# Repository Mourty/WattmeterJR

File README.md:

# WattmeterJR

This is a smaller cheaper version of the wattmeter described here https://github.com/Mourty/Wattmeter-Project

This version of the measurment board is greatly different than the original and required seperate firmware, but can interface with the service from the original just fine. This version doesn't have the super capacitor and boost converter. It also forgoes the voltage transformer in favor of a voltage divider. All parts that can be surface mount are. This is to save space and cost. The ESP32 used here also isn't a dev module and doesn't have the normal USB interface and requires a seperate UART programming device.

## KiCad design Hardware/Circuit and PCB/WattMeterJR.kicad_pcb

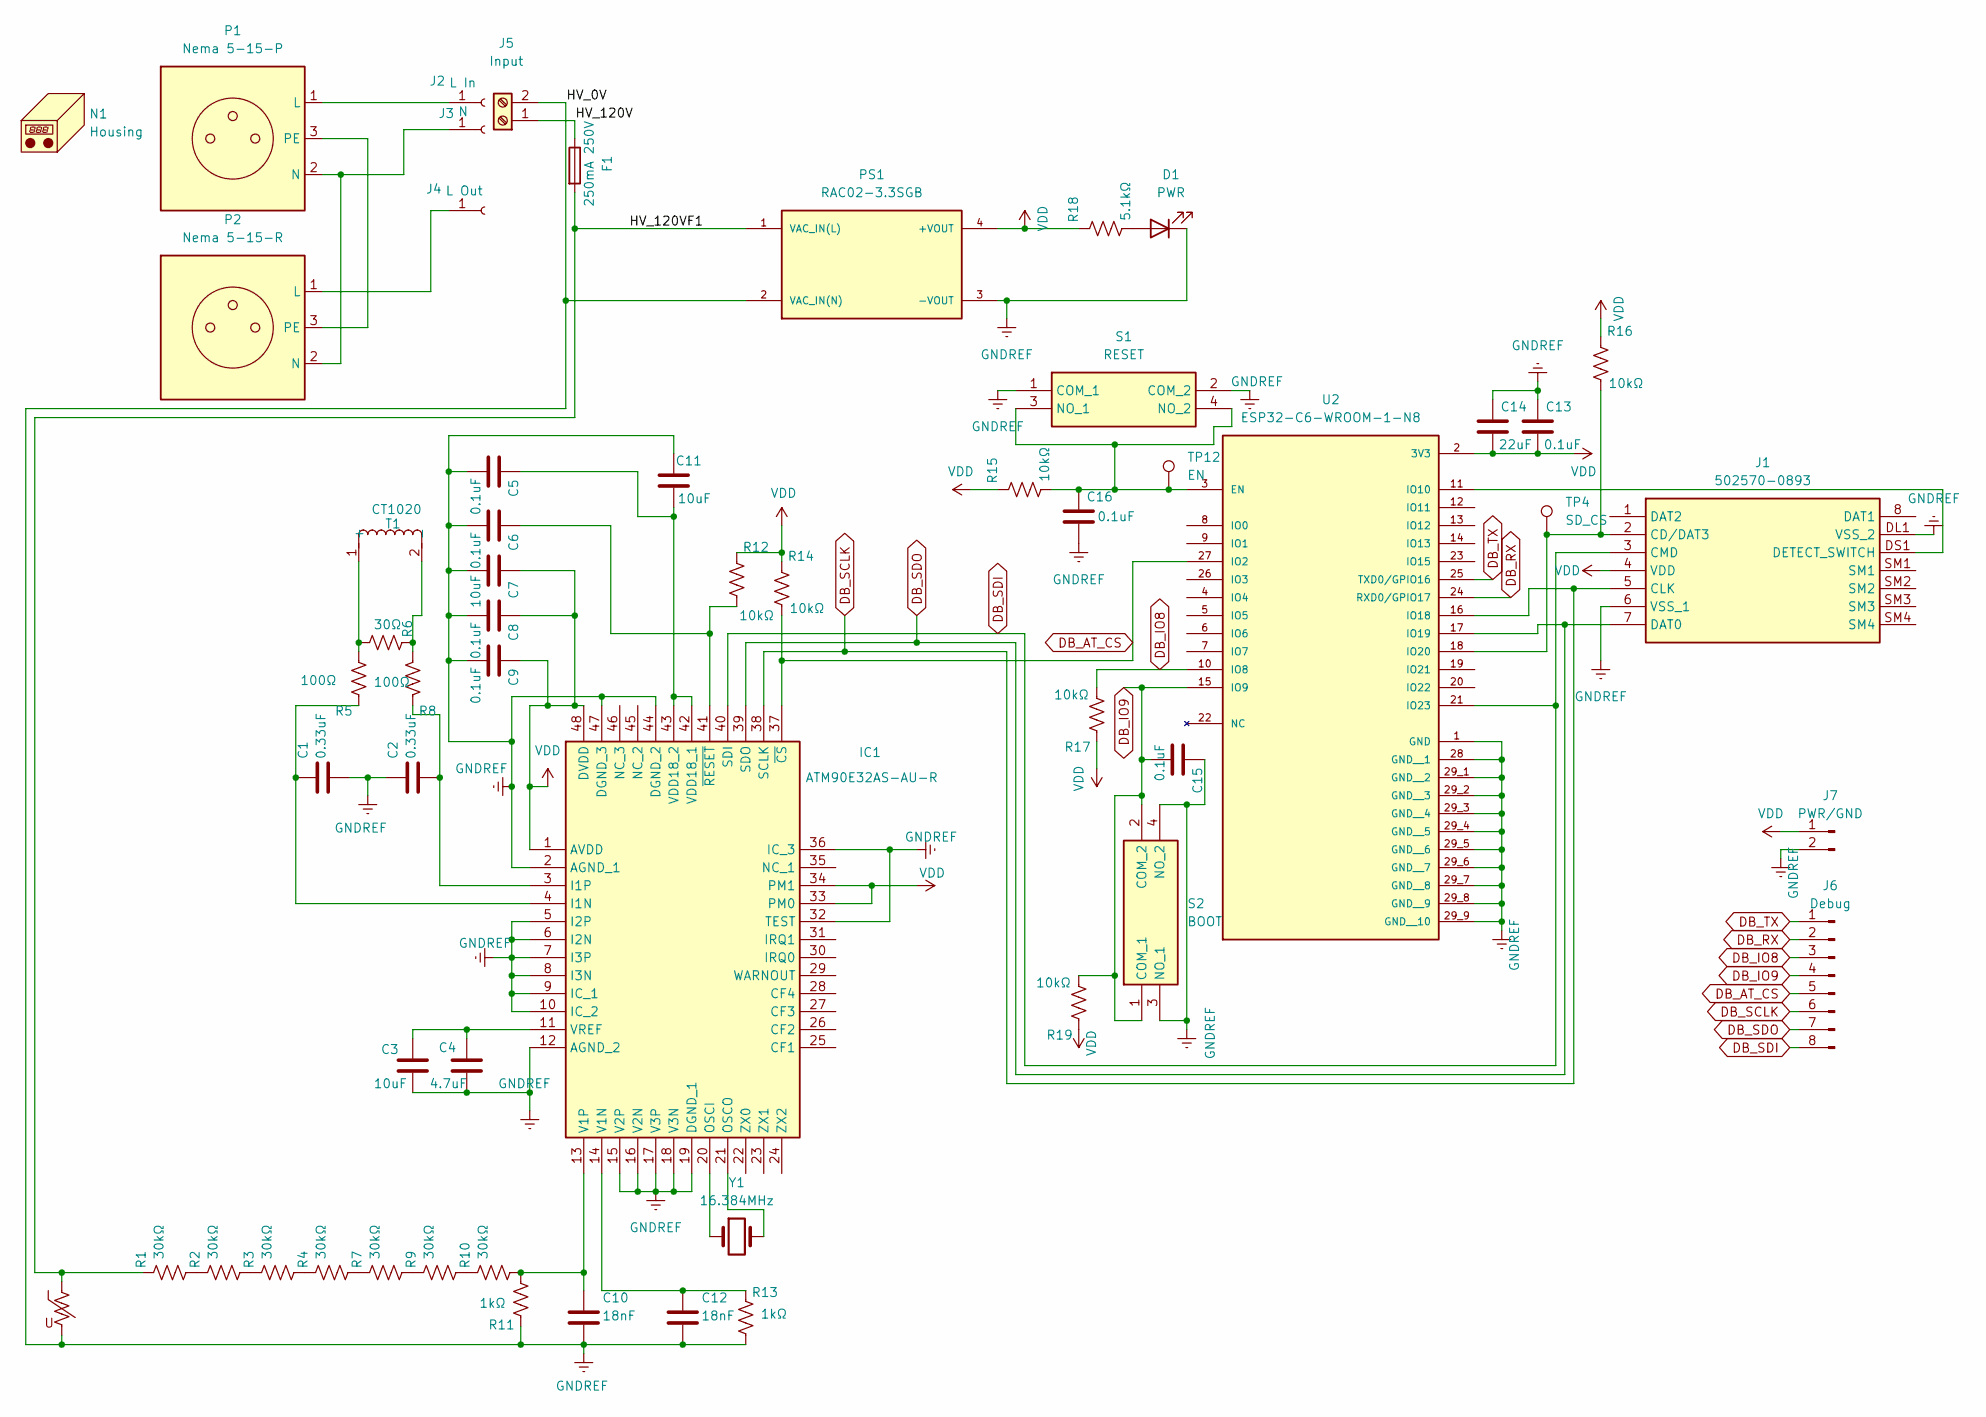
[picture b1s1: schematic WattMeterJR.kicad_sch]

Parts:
C1, C2: 0.33uF; C_0805_2012Metric_Pad1.18x1.45mm_HandSolder; Mouser# 810-FG18X7R1H334KRT6
C3, C7, C11: 10uF; C_0805_2012Metric_Pad1.18x1.45mm_HandSolder; Mouser# 810-FG18X5R1E106MR00
C4: 4.7uF; C_0805_2012Metric_Pad1.18x1.45mm_HandSolder; Mouser# 810-FG28X5R1E475KRT6
C5, C6, C8, C9, C13, C15, C16: 0.1uF; C_0805_2012Metric_Pad1.18x1.45mm_HandSolder; Mouser# 594-K104K15X7RF5WH5
C10, C12: 18nF; C_0805_2012Metric_Pad1.18x1.45mm_HandSolder; Mouser# 594-K183K10X7RF53H5
C14: 22uF; C_0805_2012Metric_Pad1.18x1.45mm_HandSolder; Mouser# 594-K104K15X7RF5WH5
D1: PWR; LED_0805_2012Metric_Pad1.15x1.40mm_HandSolder
F1: 250mA 250V; 00318231; Mouser# 576-0313.250HXP
IC1: ATM90E32AS-AU-R; QFP50P900X900X120-48N; Mouser# 556-ATM90E32AS-AU-R
J1: 502570-0893; 5025700893; Mouser Part Number 538-502570-0893
J2: L In
J3: N
J4: L Out
J5: Input; CUI_TB005-762-02BE; Mouser# 490-TB005-762-02BE
J6: Debug; PinHeader_1x08_P2.54mm_Vertical
J7: PWR/GND; PinHeader_1x02_P2.54mm_Vertical
N1: Housing; 1591XXSBK
P1: Nema 5-15-P
P2: Nema 5-15-R
PS1: RAC02-3.3SGB; CONV_RAC02-3.3SGB; PARTREV 1
R1, R2, R3, R4, R7, R9, R10: 30kΩ; R_0805_2012Metric_Pad1.20x1.40mm_HandSolder
R5, R8: 100Ω; R_0805_2012Metric_Pad1.20x1.40mm_HandSolder
R6: 30Ω; R_0805_2012Metric_Pad1.20x1.40mm_HandSolder
R11, R13: 1kΩ; R_0805_2012Metric_Pad1.20x1.40mm_HandSolder
R12, R14, R15, R16, R17, R19: 10kΩ; R_0805_2012Metric_Pad1.20x1.40mm_HandSolder
R18: 5.1kΩ; R_0805_2012Metric_Pad1.20x1.40mm_HandSolder
RV1: 130VAC; C_Disc_D8.0mm_W5.0mm_P5.00mm; Mouser# 576-V07E130P
S1: RESET; PTS526SK15SMTR2LFS; Mouser Part Number 611-PTS526SK15SMR2L
S2: BOOT; PTS526SK15SMTR2LFS; Mouser Part Number 611-PTS526SK15SMR2L
T1: CT1020; Manufacturer_Part_Number CS1100L; Digikey# 419-CT1020-ND
TP4: SD_CS; PinHeader_1x01_P2.54mm_Vertical
TP12: EN; PinHeader_1x01_P2.54mm_Vertical
U2: ESP32-C6-WROOM-1-N8; XCVR_ESP32-C6-WROOM-1-N8; PARTREV 1.0
Y1: 16.384MHz; Crystal_HC49-U_Vertical; Mouser# 815-ABL-16.384-B2

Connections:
/HV_120V: F1.1, J5.1
/HV_120VF1: F1.2, PS1.1 (VAC_IN(L)), R1.2, RV1.1
DB_AT_CS: IC1.37 (~CS), J6.5, R14.1, U2.27 (IO2)
DB_IO8: J6.3, R17.1, U2.10 (IO8)
DB_IO9: C15.2, J6.4, R19.1, S2.1 (COM_1), S2.2 (COM_2), U2.15 (IO9)
DB_RX: J6.2, U2.24 (RXD0/GPIO17)
DB_SCLK: IC1.38 (SCLK), J1.5 (CLK), J6.6, U2.16 (IO18)
DB_SDI: IC1.40 (SDI), J1.3 (CMD), J6.8, U2.21 (IO23)
DB_SDO: IC1.39 (SDO), J1.7 (DAT0), J6.7, U2.17 (IO19)
DB_TX: J6.1, U2.25 (TXD0/GPIO16)
GNDREF: C1.2, C2.1, C3.2, C4.2, C5.2, C6.2, C7.1, C8.2, C9.2, C10.2, C11.2, C12.2, C13.1, C14.1, C15.1, C16.2, D1.1 (K), IC1.2 (AGND_1), IC1.5 (I2P), IC1.6 (I2N), IC1.7 (I3P), IC1.8 (I3N), IC1.9 (IC_1), IC1.10 (IC_2), IC1.12 (AGND_2), IC1.15 (V2P), IC1.16 (V2N), IC1.17 (V3P), IC1.18 (V3N), IC1.19 (DGND_1), IC1.32 (TEST), IC1.36 (IC_3), IC1.44 (DGND_2), IC1.47 (DGND_3), J1.6 (VSS_1), J1.DL1 (VSS_2), J5.2, J7.2, PS1.2 (VAC_IN(N)), PS1.3 (-VOUT), R11.2, R13.1, RV1.2, S1.1 (COM_1), S1.2 (COM_2), S2.3 (NO_1), S2.4 (NO_2), U2.1 (GND), U2.28 (GND__1), U2.29_1 (GND__2), U2.29_2 (GND__3), U2.29_3 (GND__4), U2.29_4 (GND__5), U2.29_5 (GND__6), U2.29_6 (GND__7), U2.29_7 (GND__8), U2.29_8 (GND__9), U2.29_9 (GND__10)
unnamed: D1.2 (A), R18.1
unnamed: C1.1, IC1.4 (I1N), R5.2
unnamed: C2.2, IC1.3 (I1P), R8.2
unnamed: IC1.20 (OSCI), Y1.1
unnamed: IC1.21 (OSCO), Y1.2
unnamed: C12.1, IC1.14 (V1N), R13.2
unnamed: C10.1, IC1.13 (V1P), R10.1, R11.1
unnamed: C5.1, C11.1, IC1.42 (VDD18_1), IC1.43 (VDD18_2)
unnamed: C3.1, C4.1, IC1.11 (VREF)
unnamed: C6.1, IC1.41 (~RESET), R12.1
unnamed: J1.2 (CD/DAT3), R16.1, TP4.1, U2.18 (IO20)
unnamed: J1.DS1 (DETECT_SWITCH), U2.11 (IO10)
unnamed: J2.1, P1.1 (L)
unnamed: J3.1, P1.2 (N), P2.2 (N)
unnamed: J4.1, P2.1 (L)
unnamed: P1.3 (PE), P2.3 (PE)
unnamed: R1.1, R2.2
unnamed: R2.1, R3.2
unnamed: R3.1, R4.2
unnamed: R4.1, R7.2
unnamed: R7.1, R9.2
unnamed: R9.1, R10.2
unnamed: C16.1, R15.1, S1.3 (NO_1), S1.4 (NO_2), TP12.1, U2.3 (EN)
unnamed: R5.1, R6.1, T1.1 (+)
unnamed: R6.2, R8.1, T1.2 (-)
VDD: C7.2, C8.1, C9.1, C13.2, C14.2, IC1.1 (AVDD), IC1.33 (PM0), IC1.34 (PM1), IC1.48 (DVDD), J1.4 (VDD), J7.1, PS1.4 (+VOUT), R12.2, R14.2, R15.2, R16.2, R17.2, R18.2, R19.2, U2.2 (3V3)

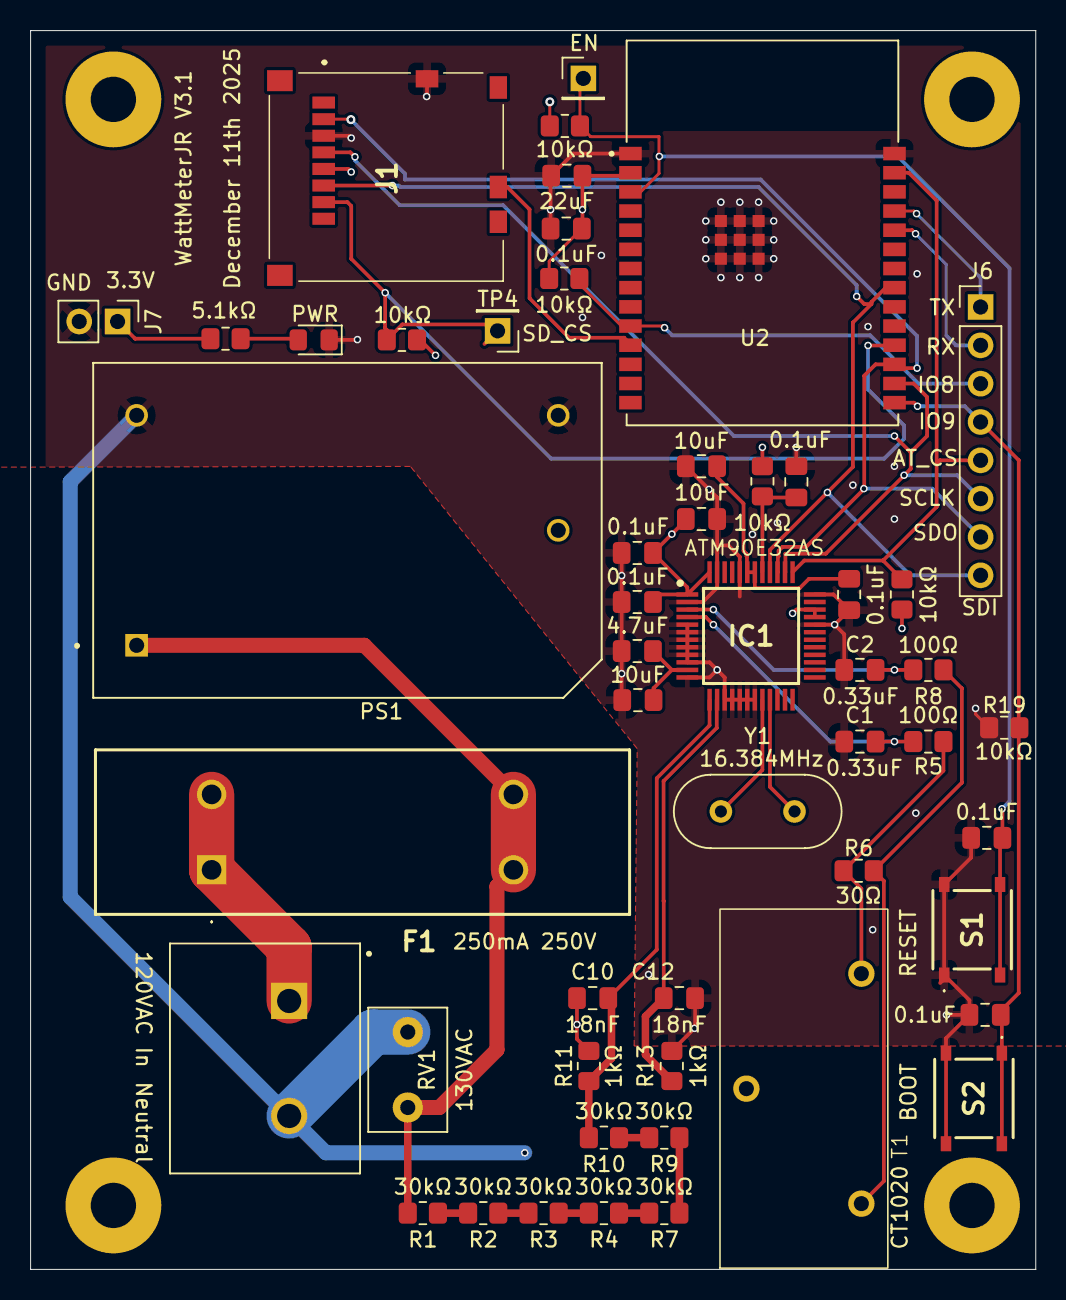
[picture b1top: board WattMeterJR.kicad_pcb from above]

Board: 4 copper layers, 66.6 x 82.1 mm, 52 parts (0 on the bottom side), 33 nets.

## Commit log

2026-01-04 Add Pictures
2026-01-04 Add pullup for GPIO9
2026-01-04 fix board render
